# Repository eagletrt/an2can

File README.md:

# Analog to CAN converter

Standalone system capable of performing analog-to-digital conversion and preprocessing and output data over CAN BUS

## Contributors
Latest to oldest:
- Thomas Nonis

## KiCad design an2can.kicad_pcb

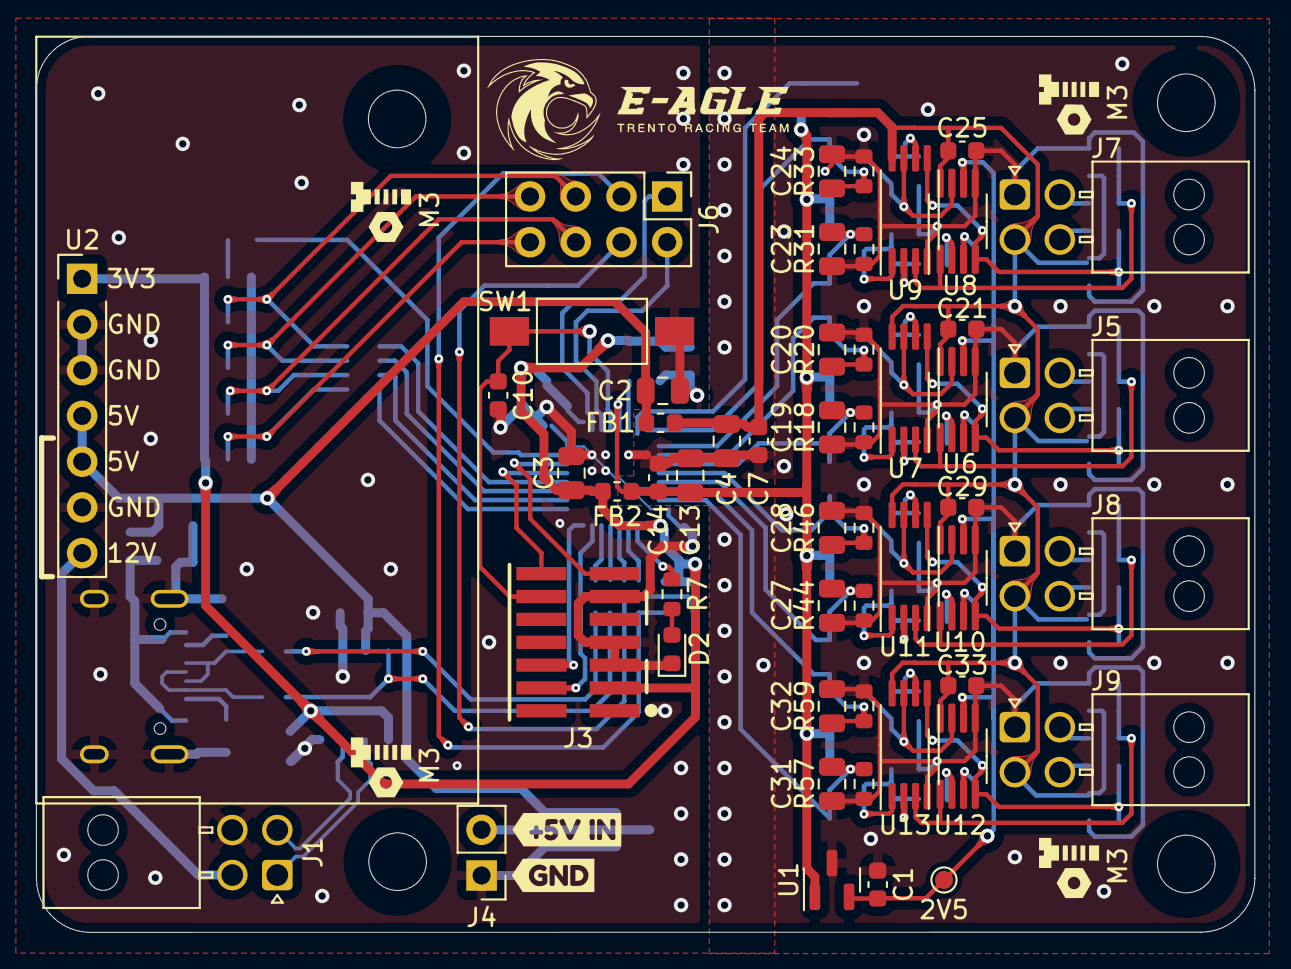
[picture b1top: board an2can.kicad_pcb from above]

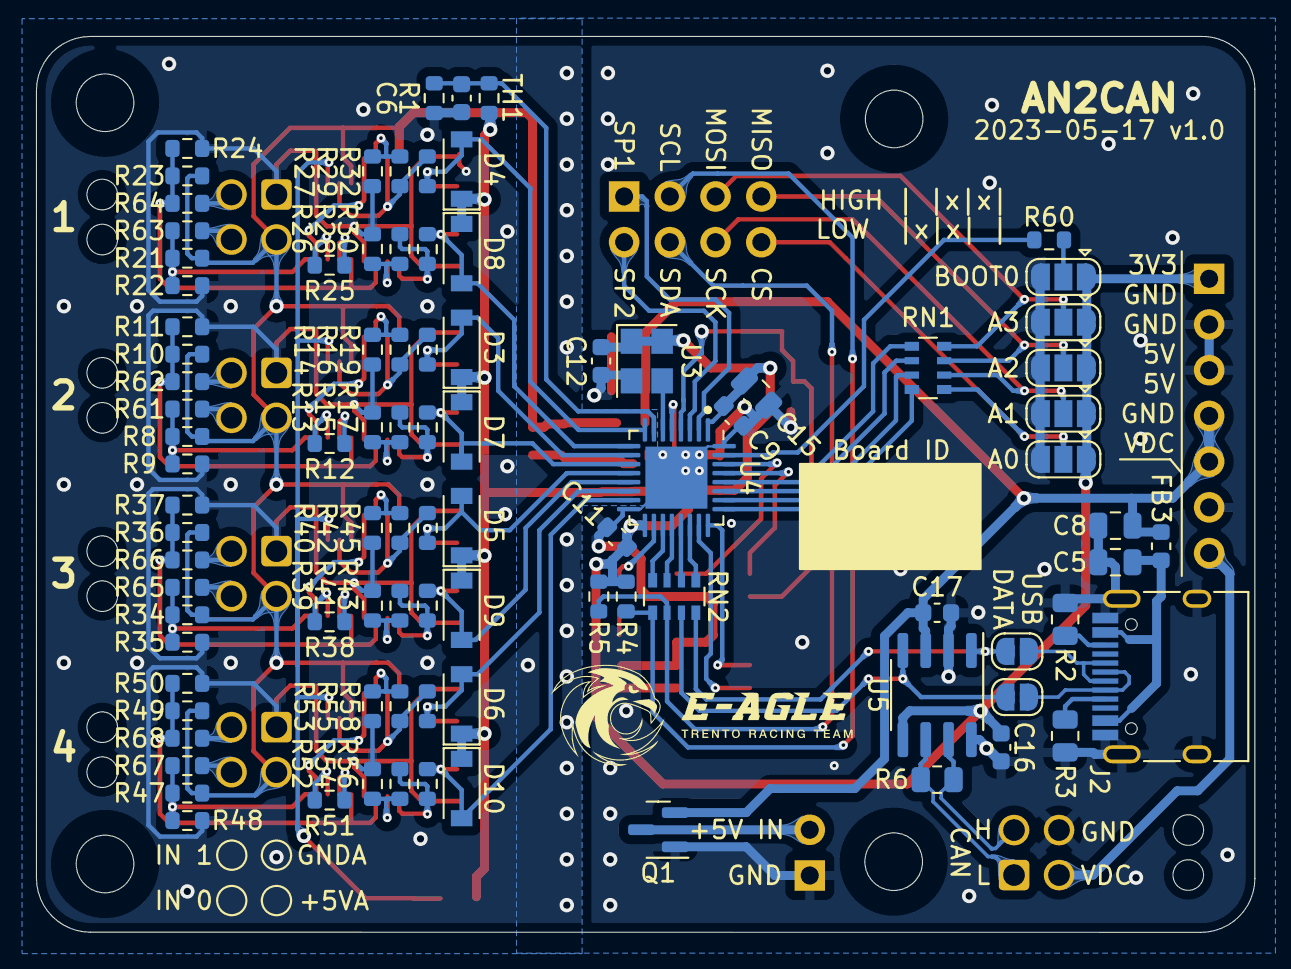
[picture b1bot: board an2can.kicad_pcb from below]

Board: 2 copper layers, 67.7 x 49.8 mm, 150 parts (92 on the bottom side), 93 nets.

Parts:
C1, C6, C9, C10, C11, C12, C14, C16, C17, C21, C25, C29, C33: 100n; C_0603_1608Metric
C2, C3, C4, C5, C8, C19, C20, C23, C24, C27, C28, C31, C32: C; C_0805_2012Metric
C7: C; C_0603_1608Metric
C13: 1u; C_0805_2012Metric
C15: 10u; C_0805_2012Metric
D2: USER LED; LED_0603_1608Metric
D3, D4, D5, D6, D7, D8, D9, D10: D_Schottky; D_SOD-123
FB1, FB2, FB3: FerriteBead; L_0603_1608Metric
H1, H2, H3: MountingHole; MountingHole_3.2mm_M3_ISO14580
J1: PWR/CAN; Molex_Nano-Fit_105314-xx04_2x02_P2.50mm_Horizontal
J2: USB C; USB_C_Receptacle_HRO_TYPE-C-31-M-12
J3: DBG; SAMTEC_FTSH-107-01-L-DV-K-TR
J4: 5V IN; PinHeader_1x02_P2.54mm_Vertical
J5, J7, J8, J9: Input; Molex_Nano-Fit_105314-xx04_2x02_P2.50mm_Horizontal
J6: Aux; PinHeader_2x04_P2.54mm_Vertical
JP1: A0; SolderJumper-3_P1.3mm_Open_RoundedPad1.0x1.5mm
JP2: A1; SolderJumper-3_P1.3mm_Open_RoundedPad1.0x1.5mm
JP3: A2; SolderJumper-3_P1.3mm_Open_RoundedPad1.0x1.5mm
JP4: A3; SolderJumper-3_P1.3mm_Open_RoundedPad1.0x1.5mm
JP5: BOOT0; SolderJumper-3_P1.3mm_Open_RoundedPad1.0x1.5mm
JP6: USB N; SolderJumper-2_P1.3mm_Open_RoundedPad1.0x1.5mm
JP7: USB P; SolderJumper-2_P1.3mm_Open_RoundedPad1.0x1.5mm
NT1: Net Tie; NetTie-2_SMD_Pad0.5mm
Q1: PMV65XP; SOT-23
R1, R4, R5, R13, R14, R15, R16, R17, R18, R19, R20, R26, R27, R28, R29, R30, R31, R32, R33, R39, R40, R41, R42, R43, R44, R45, R46, R52, R53, R54, R55, R56, R57, R58, R59, R60, R61, R62, R63, R64, R65, R66, R67, R68: R; R_0603_1608Metric
R2, R3: 5k1; R_0805_2012Metric
R6: 120; R_0805_2012Metric
R7: 1k; R_0603_1608Metric
R8, R9, R10, R11, R21, R22, R23, R24, R34, R35, R36, R37, R47, R48, R49, R50: 120 0.1%; R_0603_1608Metric
R12, R25, R38, R51: 220k 0.1%; R_0603_1608Metric
RN1, RN2: R; R_Array_Convex_4x0603
SW1: RESET; SW_SPST_FSMSM
TH1: Thermistor; R_0603_1608Metric
TP1: Offset; TestPoint_Pad_D1.0mm
U1: MAX6025; SOT-23
U2: Tex_DCDC_v2; Tex_DCDC_v2_horizontal
U3: DSC61XX; Crystal_SMD_3225-4Pin_3.2x2.5mm
U4: STM32L432KCUx; QFN-32-1EP_5x5mm_P0.5mm_EP3.45x3.45mm
U5: MCP2562FD; SOIC-8_3.9x4.9mm_P1.27mm
U6, U8, U10, U12: AD8221ARZ; MSOP-8_3x3mm_P0.65mm
U7, U9, U11, U13: Opamp_Dual; TSSOP-8_4.4x3mm_P0.65mm
kibuzzard-645FEBDB: G***; kibuzzard-645FEBDB
kibuzzard-645FEBF3: G***; kibuzzard-645FEBF3

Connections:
+3.3VA: C13.1, C14.1, D3.1 (K), D4.1 (K), D5.1 (K), D6.1 (K), D7.1 (K), D8.1 (K), D9.1 (K), D10.1 (K), FB2.2, TH1.1, U1.1 (IN), U4.5 (VDDA)
+3V3: C3.1, C9.1, C11.1, C12.1, C15.1, C16.1, FB2.1, J3.3 (VCC), JP1.1 (A), JP2.1 (A), JP3.1 (A), JP4.1 (A), JP5.1 (A), R4.1, R5.1, U2.1 (3V3), U3.1 (OE), U3.4 (VDD), U4.1 (VDD), U4.17 (VDD), U5.5 (Vio)
+5V: C2.1, C8.1, C17.1, FB1.1, FB3.2, Q1.2 (S), U2.4 (5V), U2.5 (5V), U5.3 (VDD)
+5VA: C4.1, C7.1, C21.2, C25.2, C29.2, C33.2, FB1.2, J5.2, J7.2, J8.2, J9.2, R8.1, R10.1, R21.1, R23.1, R34.1, R36.1, R47.1, R49.1, U6.8 (Vs+), U7.8 (V+), U8.8 (Vs+), U9.8 (V+), U10.8 (Vs+), U11.8 (V+), U12.8 (Vs+), U13.8 (V+)
/2V5_OFFSET: C1.2, TP1.1, U1.2 (OUT), U6.6 (Ref), U8.6 (Ref), U10.6 (Ref), U12.6 (Ref)
/A0: J6.8, JP1.2 (C), RN1.5 (R4.2)
/A1: J6.6, JP2.2 (C), RN1.6 (R3.2)
/A2: J6.7, JP3.2 (C), RN1.7 (R2.2)
/A3: J6.5, JP4.2 (C), RN1.8 (R1.2)
/CAN+: J1.2, R6.2, U5.7 (CANH)
/CAN-: J1.1, R6.1, U5.6 (CANL)
/Input Stage 1/IN_0: J7.4, R63.1
/Input Stage 1/IN_0+: R21.2, R22.1, R63.2, U8.4 (+), U9.5 (+)
/Input Stage 1/IN_0-: R27.1, R29.2, U9.6 (-)
/Input Stage 1/IN_1: J7.3, R64.2
/Input Stage 1/IN_1+: R23.2, R24.1, R64.1, U8.1 (-), U9.3 (+)
/Input Stage 1/IN_1-: R26.1, R28.2, U9.2 (-)
/Input Stage 1/OUT_COM: C24.1, D4.2 (A), R32.2, R33.1, U4.8 (PA2)
/Input Stage 1/OUT_COM_UNFLT: R29.1, R32.1, U8.7, U9.7
/Input Stage 1/OUT_SINGLE: C23.1, D8.2 (A), R30.1, R31.1, U4.9 (PA3)
/Input Stage 1/OUT_SINGLE_UNFLT: R28.1, R30.2, U9.1
/Input Stage 1/RG1: R25.1, U8.2 (Rg)
/Input Stage 1/RG2: R25.2, U8.3 (Rg)
/Input Stage 2/IN_0: J5.4, R61.1
/Input Stage 2/IN_0+: R8.2, R9.1, R61.2, U6.4 (+), U7.5 (+)
/Input Stage 2/IN_0-: R14.1, R16.2, U7.6 (-)
/Input Stage 2/IN_1: J5.3, R62.2
/Input Stage 2/IN_1+: R10.2, R11.1, R62.1, U6.1 (-), U7.3 (+)
/Input Stage 2/IN_1-: R13.1, R15.2, U7.2 (-)
/Input Stage 2/OUT_COM: C20.1, D3.2 (A), R19.2, R20.1, U4.10 (PA4)
/Input Stage 2/OUT_COM_UNFLT: R16.1, R19.1, U6.7, U7.7
/Input Stage 2/OUT_SINGLE: C19.1, D7.2 (A), R17.1, R18.1, U4.11 (PA5)
/Input Stage 2/OUT_SINGLE_UNFLT: R15.1, R17.2, U7.1
/Input Stage 2/RG1: R12.1, U6.2 (Rg)
/Input Stage 2/RG2: R12.2, U6.3 (Rg)
/Input Stage 3/IN_0: J8.4, R65.1
/Input Stage 3/IN_0+: R34.2, R35.1, R65.2, U10.4 (+), U11.5 (+)
/Input Stage 3/IN_0-: R40.1, R42.2, U11.6 (-)
/Input Stage 3/IN_1: J8.3, R66.2
/Input Stage 3/IN_1+: R36.2, R37.1, R66.1, U10.1 (-), U11.3 (+)
/Input Stage 3/IN_1-: R39.1, R41.2, U11.2 (-)
/Input Stage 3/OUT_COM: C28.1, D5.2 (A), R45.2, R46.1, U4.12 (PA6)
/Input Stage 3/OUT_COM_UNFLT: R42.1, R45.1, U10.7, U11.7
/Input Stage 3/OUT_SINGLE: C27.1, D9.2 (A), R43.1, R44.1, U4.13 (PA7)
/Input Stage 3/OUT_SINGLE_UNFLT: R41.1, R43.2, U11.1
/Input Stage 3/RG1: R38.1, U10.2 (Rg)
/Input Stage 3/RG2: R38.2, U10.3 (Rg)
/Input Stage 4/IN_0: J9.4, R67.1
/Input Stage 4/IN_0+: R47.2, R48.1, R67.2, U12.4 (+), U13.5 (+)
/Input Stage 4/IN_0-: R53.1, R55.2, U13.6 (-)
/Input Stage 4/IN_1: J9.3, R68.2
/Input Stage 4/IN_1+: R49.2, R50.1, R68.1, U12.1 (-), U13.3 (+)
/Input Stage 4/IN_1-: R52.1, R54.2, U13.2 (-)
/Input Stage 4/OUT_COM: C32.1, D6.2 (A), R58.2, R59.1, U4.14 (PB0)
/Input Stage 4/OUT_COM_UNFLT: R55.1, R58.1, U12.7, U13.7
/Input Stage 4/OUT_SINGLE: C31.1, D10.2 (A), R56.1, R57.1, U4.15 (PB1)
/Input Stage 4/OUT_SINGLE_UNFLT: R54.1, R56.2, U13.1
/Input Stage 4/RG1: R51.1, U12.2 (Rg)
/Input Stage 4/RG2: R51.2, U12.3 (Rg)
/MCU/+5V_USB_UNFILTERED: C5.1, FB3.1, J2.A4 (VBUS), J2.A9 (VBUS), J2.B4 (VBUS), J2.B9 (VBUS)
/MCU/BOOT0: R60.2, U4.31 (PH3)
/MCU/CAN_RX: JP6.1 (A), RN2.3 (R3.1), U5.4 (RXD)
/MCU/CAN_TX: JP7.1 (A), RN2.4 (R4.1), U5.1 (TXD)
/MCU/CLK: U3.3 (OUT), U4.6 (PA0)
/MCU/DBG_RX: J3.13 (VCP_RX), U4.30 (PB7)
/MCU/DBG_TX: J3.14 (VCP_TX), U4.29 (PB6)
/MCU/I2C_SCL: J6.3, R4.2, RN2.1 (R1.1)
/MCU/I2C_SDA: J6.4, R5.2, RN2.2 (R2.1)
/MCU/SWCLK: J3.6 (JCLK/SWCLK), U4.24 (PA14)
/MCU/SWDIO: J3.4 (JTMS/SWDIO), U4.23 (PA13)
/MCU/Spare1: J6.1, U4.2 (PC14)
/MCU/Spare2: J6.2, U4.3 (PC15)
/MCU/USB_N: J2.A7 (D-), J2.B7 (D-), JP6.2 (B)
/MCU/USB_P: J2.A6 (D+), J2.B6 (D+), JP7.2 (B)
/MCU/USER_LED: R7.1, U4.18 (PA8)
/MCU/~RESET: C10.1, J3.12 (~RST), SW1.2, U4.4 (NRST)
/Temp: C6.2, R1.1, TH1.2, U4.7 (PA1)
GND: C2.2, C3.2, C5.2, C8.2, C9.2, C10.2, C11.2, C12.2, C15.2, C16.2, C17.2, D2.1 (K), J1.4, J2.A1 (GND), J2.A12 (GND), J2.B1 (GND), J2.B12 (GND), J2.S1 (SHIELD), J3.5 (GND), J3.7 (GND), J3.11 (GNDDetect), J4.1, JP1.3 (B), JP2.3 (B), JP3.3 (B), JP4.3 (B), JP5.3 (B), NT1.1, Q1.1 (G), R2.2, R3.2, SW1.1, U2.2 (GND), U2.3 (GND), U2.6 (GND), U3.2 (GND), U4.16 (VSS), U4.32 (VSS), U4.33 (VSS), U5.2 (VSS), U5.8 (STBY)
GNDA: C1.1, C4.2, C6.1, C7.2, C13.2, C14.2, C19.2, C20.2, C21.1, C23.2, C24.2, C25.1, C27.2, C28.2, C29.1, C31.2, C32.2, C33.1, J5.1, J7.1, J8.1, J9.1, NT1.2, R1.2, R9.2, R11.2, R13.2, R14.2, R18.2, R20.2, R22.2, R24.2, R26.2, R27.2, R31.2, R33.2, R35.2, R37.2, R39.2, R40.2, R44.2, R46.2, R48.2, R50.2, R52.2, R53.2, R57.2, R59.2, U1.3 (GND), U6.5 (Vs-), U7.4 (V-), U8.5 (Vs-), U9.4 (V-), U10.5 (Vs-), U11.4 (V-), U12.5 (Vs-), U13.4 (V-)
unnamed: D2.2 (A), R7.2
unnamed: J2.A5 (CC1), R3.1
unnamed: J2.B5 (CC2), R2.1
unnamed: J4.2, Q1.3 (D)
unnamed: JP5.2 (C), R60.1
unnamed: RN1.1 (R1.1), U4.28 (PB5)
unnamed: RN1.2 (R2.1), U4.27 (PB4)
unnamed: RN1.3 (R3.1), U4.26 (PB3)
unnamed: RN1.4 (R4.1), U4.25 (PA15)
unnamed: RN2.5 (R4.2), U4.22 (PA12)
unnamed: RN2.6 (R3.2), U4.21 (PA11)
unnamed: RN2.7 (R2.2), U4.20 (PA10)
unnamed: RN2.8 (R1.2), U4.19 (PA9)
VDC: J1.3, U2.7 (VIN)

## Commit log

2023-04-22 chore: edit template for project
2023-04-22 sch: first draft of mcu configuration
2023-04-22 doc: add datasheets
2023-04-23 sch: add opamps
2023-04-23 sch: change to stm32l432k and change analog input topology
2023-04-23 doc: update datasheets and appnotes
2023-04-25 sch: input stage sheets
2023-05-01 doc: add vref datasheet
2023-05-01 sch: add power delivery network and finalize schematic
2023-05-01 pcb: draft digital section and partial analog
2023-05-01 sch: change single input connector to 4 02x02
2023-05-01 pcb: full draft of positioning
2023-05-08 sch: delete old ina sheet
2023-05-08 sch: add input series resistor to form divider and clamp to opamp output
2023-05-08 pcb: define routing of input stage
2023-05-09 pcb: finalize routing of analog section
2023-05-11 pcb: continue routing of digital section
2023-05-13 pcb: complete routing, add silkscreen details, finalize board
2023-05-17 pcb: change oscillator footprint, add board id pad and move board name on back silkscreen
2023-05-17 pcb: add teardrops
2023-05-25 prod: generate v1.0 gerbers
2023-08-29 lib:add molex 3d models
